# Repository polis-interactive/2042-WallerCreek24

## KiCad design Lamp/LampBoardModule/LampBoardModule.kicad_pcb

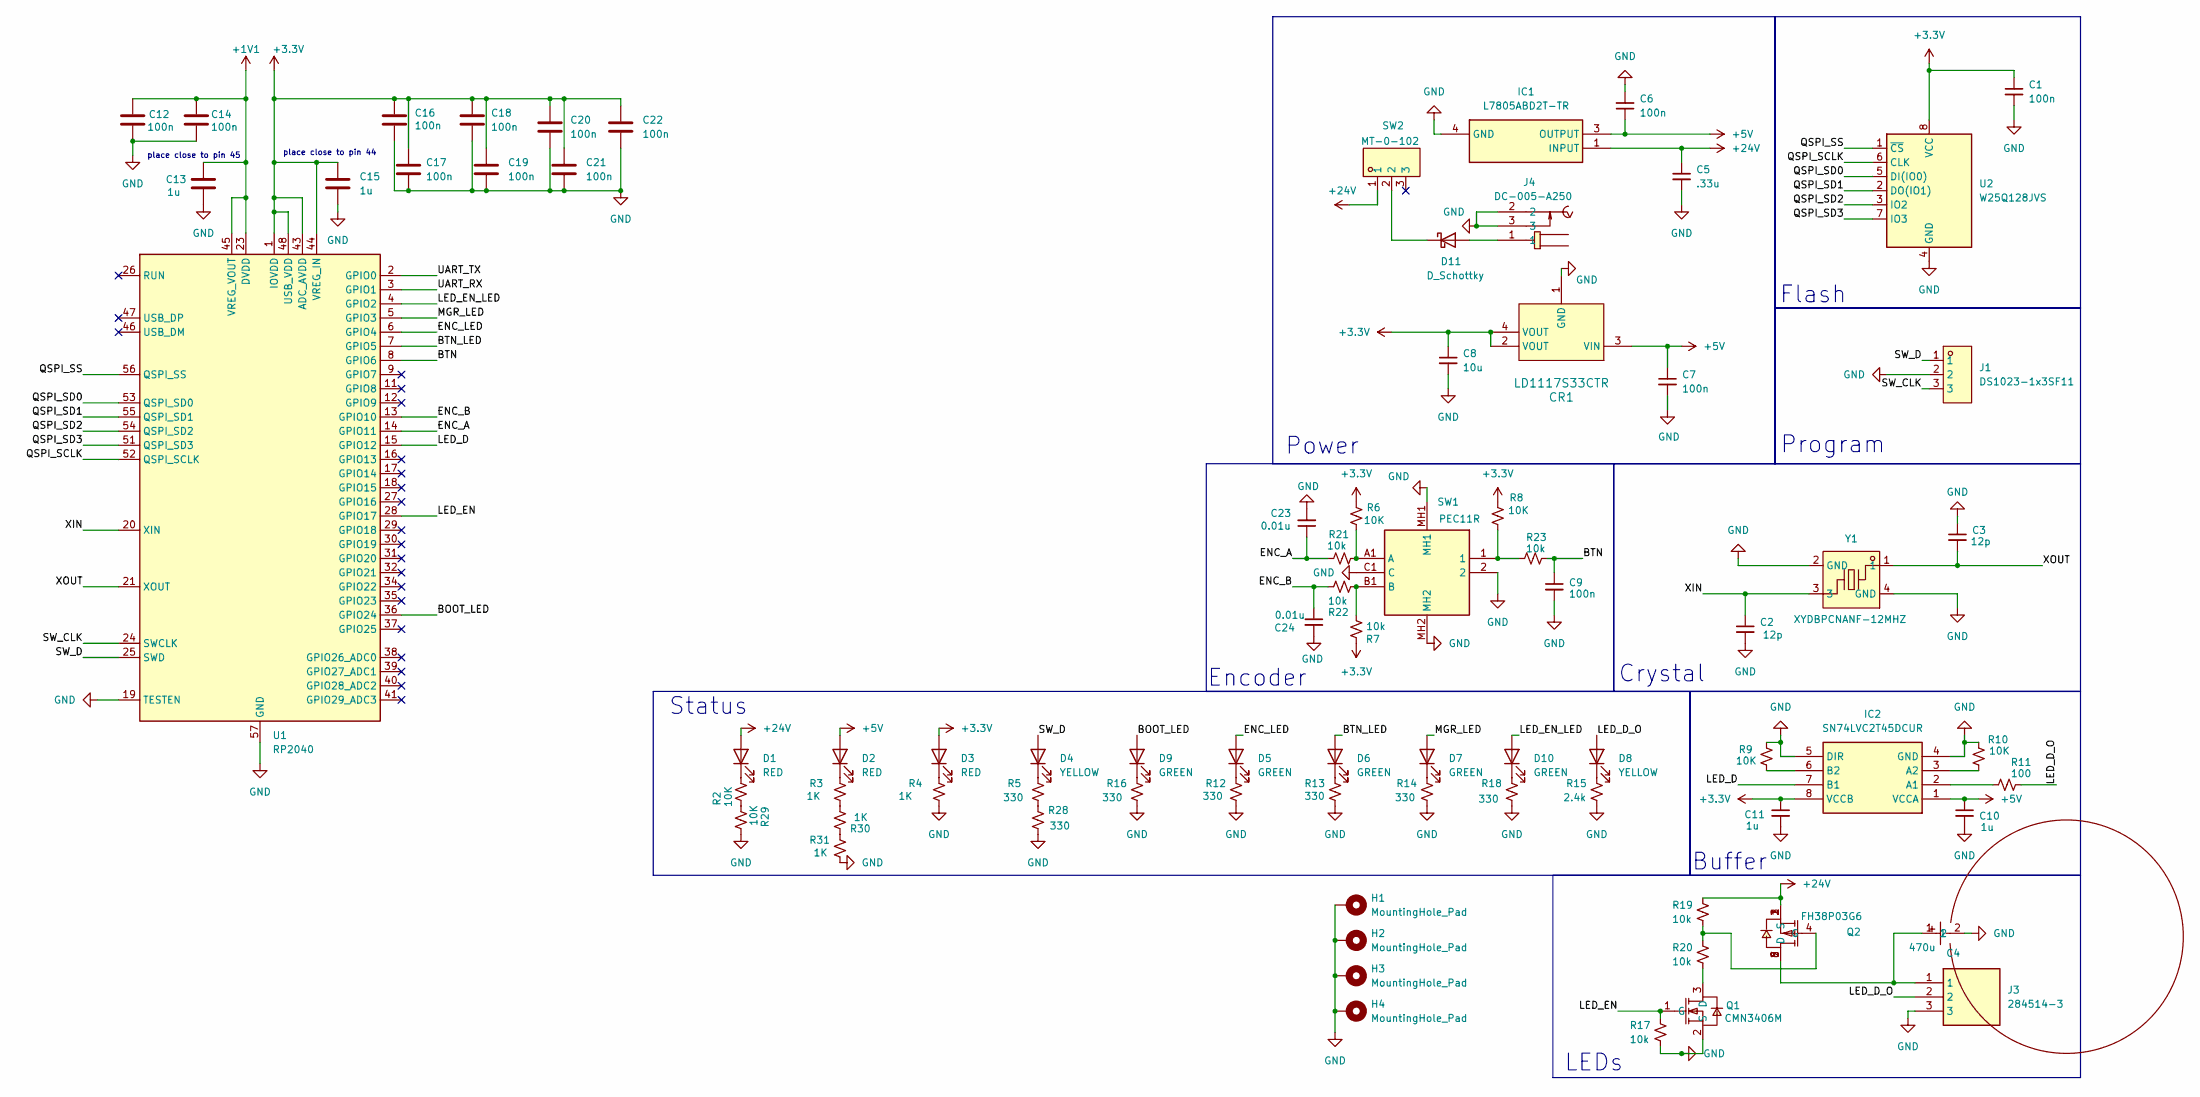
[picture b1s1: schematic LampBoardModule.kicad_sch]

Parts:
C1, C6, C7, C9, C12, C14, C16, C17, C18, C19, C21, C22: 100n; C_0402_1005Metric; LCSC C1525
C2, C3: 12p; C_0402_1005Metric; LCSC C1547
C4: 470u; CAP-TH_BD10.0-P5.00-D1.0-FD; LCSC Part C34642
C5: .33u; C_0805_2012Metric; LCSC C309049
C8: 10u; C_0603_1608Metric; LCSC C92487
C10, C11, C13, C15: 1u; C_0402_1005Metric; LCSC C52923
C20: 100n; C_0402_1005Metric; JLCPCBA Part # C1525
C23, C24: 0.01u; C_0603_1608Metric; LCSC C1589
CR1: LD1117S33CTR; SOT-223-4_L6.5-W3.5-P2.30-LS7.0-BR; LCSC C35879
D1, D2, D3: RED; LED_0603_1608Metric; LCSC C2286
D4, D8: YELLOW; LED_0603_1608Metric; LCSC C965808
D5, D6, D7, D9, D10: GREEN; LED_0603_1608Metric; LCSC C965804
D11: D_Schottky; D_SMA; LCSC C8678
H1, H2, H3, H4: MountingHole_Pad; MountingHole_2.7mm_M2.5_DIN965_Pad
IC1: L7805ABD2T-TR; D2PAK-STB35NF10T4; Mouser Part Number 511-L7805ABD2T-TR
IC2: SN74LVC2T45DCUR; SOP50P310X90-8N; Mouser Part Number 595-SN74LVC2T45DCUR
J1: DS1023-1x3SF11; HDR-TH_3P-P2.54-V-F-1; LCSC Part C7509516
J3: 284514-3; SHDR3W80P0X350_1X3_1250X725X940P; Mouser Part Number 571-284514-3
J4: DC-005-A250; DC-IN-TH_DC-005-A250; LCSC Part C720558
Q1: CMN3406M; SOT-23-3_L2.9-W1.3-P0.95-LS2.4-BR; LCSC Part C5203800
Q2: FH38P03G6; DFN-8_L3.3-W3.3-P0.65-BL-EP; LCSC Part C2929033
R2, R6, R8, R9, R10, R29: 10K; R_0603_1608Metric; LCSC C15401
R3, R4, R30, R31: 1K; R_0402_1005Metric; LCSC C25543
R5, R12, R13, R14, R16, R18, R28: 330; R_0603_1608Metric; LCSC C23138
R7, R17, R19, R20, R21, R22, R23: 10k; R_0603_1608Metric; LCSC C15401
R11: 100; R_0603_1608Metric; LCSC C22775
R15: 2.4k; R_0805_2012Metric; LCSC C17526
SW1: PEC11R; PEC11R4220FS0024; Mouser Part Number 652-PEC11R-4220F-S24
SW2: MT-0-102; SW-TH_MT-0-102-E001-T000-RS-PJ; LCSC Part C1788499
U1: RP2040; QFN-56-1EP_7x7mm_P0.4mm_EP3.2x3.2mm; LCSC C2040
U2: W25Q128JVS; SOIC-8_5.23x5.23mm_P1.27mm; LCSC C97521
Y1: XYDBPCNANF-12MHZ; OSC-SMD_4P-L2.5-W2.0-BL; Mouser Part Number 815-ABM8-272-T3

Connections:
+1V1: C12.1, C13.1, C14.1, U1.23 (DVDD), U1.45 (VREG_VOUT), U1.50 (DVDD)
+3.3V: C1.1, C8.1, C11.1, C15.1, C16.1, C17.1, C18.1, C19.1, C20.1, C21.1, C22.1, CR1.2 (VOUT), CR1.4 (VOUT), D3.2 (A), IC2.8 (VCCB), R6.2, R7.2, R8.2, U1.1 (IOVDD), U1.10 (IOVDD), U1.22 (IOVDD), U1.33 (IOVDD), U1.42 (IOVDD), U1.43 (ADC_AVDD), U1.44 (VREG_IN), U1.48 (USB_VDD), U1.49 (IOVDD), U2.8 (VCC)
+5V: C6.1, C7.1, C10.1, CR1.3 (VIN), D2.2 (A), IC1.3 (OUTPUT), IC2.1 (VCCA)
+24V: C5.1, D1.2 (A), IC1.1 (INPUT), Q2.1 (S), Q2.2 (S), Q2.3 (S), R19.2, SW2.1
/BOOT_LED: D9.2 (A), U1.36 (GPIO24)
/BTN: C9.1, R23.1, U1.8 (GPIO6)
/BTN_LED: D6.2 (A), U1.7 (GPIO5)
/ENC_A: C23.1, R21.1, U1.14 (GPIO11)
/ENC_B: C24.1, R22.2, U1.13 (GPIO10)
/ENC_LED: D5.2 (A), U1.6 (GPIO4)
/LED_D: IC2.7 (B1), U1.15 (GPIO12)
/LED_D_O: D8.2 (A), J3.2, R11.1
/LED_EN: Q1.1 (G), R17.2, U1.28 (GPIO17)
/LED_EN_LED: D10.2 (A), U1.4 (GPIO2)
/MGR_LED: D7.2 (A), U1.5 (GPIO3)
/QSPI_SCLK: U1.52 (QSPI_SCLK), U2.6 (CLK)
/QSPI_SD0: U1.53 (QSPI_SD0), U2.5 (DI(IO0))
/QSPI_SD1: U1.55 (QSPI_SD1), U2.2 (DO(IO1))
/QSPI_SD2: U1.54 (QSPI_SD2), U2.3 (IO2)
/QSPI_SD3: U1.51 (QSPI_SD3), U2.7 (IO3)
/QSPI_SS: U1.56 (QSPI_SS), U2.1 (~CS)
/SW_CLK: J1.3, U1.24 (SWCLK)
/SW_D: D4.2 (A), J1.1, U1.25 (SWD)
/UART_RX: U1.3 (GPIO1)
/UART_TX: U1.2 (GPIO0)
/XIN: C2.1, U1.20 (XIN), Y1.3
/XOUT: C3.2, U1.21 (XOUT), Y1.1
GND: C1.2, C2.2, C3.1, C4.2, C5.2, C6.2, C7.2, C8.2, C9.2, C10.2, C11.2, C12.2, C13.2, C14.2, C15.2, C16.2, C17.2, C18.2, C19.2, C20.2, C21.2, C22.2, C23.2, C24.2, CR1.1 (GND), H1.1, H2.1, H3.1, H4.1, IC1.4 (GND), IC2.4 (GND), IC2.5 (DIR), J1.2, J3.3, J4.2, J4.3, Q1.2 (S), R4.2, R9.1, R10.1, R12.2, R13.2, R14.2, R15.2, R16.2, R17.1, R18.2, R28.1, R29.2, R31.2, SW1.2, SW1.C1 (C), SW1.MH1, SW1.MH2, U1.19 (TESTEN), U1.57 (GND), U2.4 (GND), Y1.2 (GND), Y1.4 (GND)
unnamed: C4.1, J3.1, Q2.5 (D), Q2.6 (D), Q2.7 (D), Q2.8 (D)
unnamed: D1.1 (K), R2.2
unnamed: D2.1 (K), R3.1
unnamed: D3.1 (K), R4.1
unnamed: D4.1 (K), R5.1
unnamed: D5.1 (K), R12.1
unnamed: D6.1 (K), R13.1
unnamed: D7.1 (K), R14.1
unnamed: D8.1 (K), R15.1
unnamed: D9.1 (K), R16.1
unnamed: D10.1 (K), R18.1
unnamed: D11.2 (A), J4.1
unnamed: D11.1 (K), SW2.2
unnamed: IC2.2 (A1), R11.2
unnamed: IC2.3 (A2), R10.2
unnamed: IC2.6 (B2), R9.2
unnamed: Q1.3 (D), R20.1
unnamed: Q2.4 (G), R19.1, R20.2
unnamed: R2.1, R29.1
unnamed: R3.2, R30.2
unnamed: R8.1, R23.2, SW1.1
unnamed: R5.2, R28.2
unnamed: R30.1, R31.1
unnamed: R6.1, R21.2, SW1.A1 (A)
unnamed: R7.1, R22.1, SW1.B1 (B)

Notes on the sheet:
Crystal
place close to pin 44
Buffer
Power
place close to pin 45
LEDs
Flash
Status
Program
Encoder

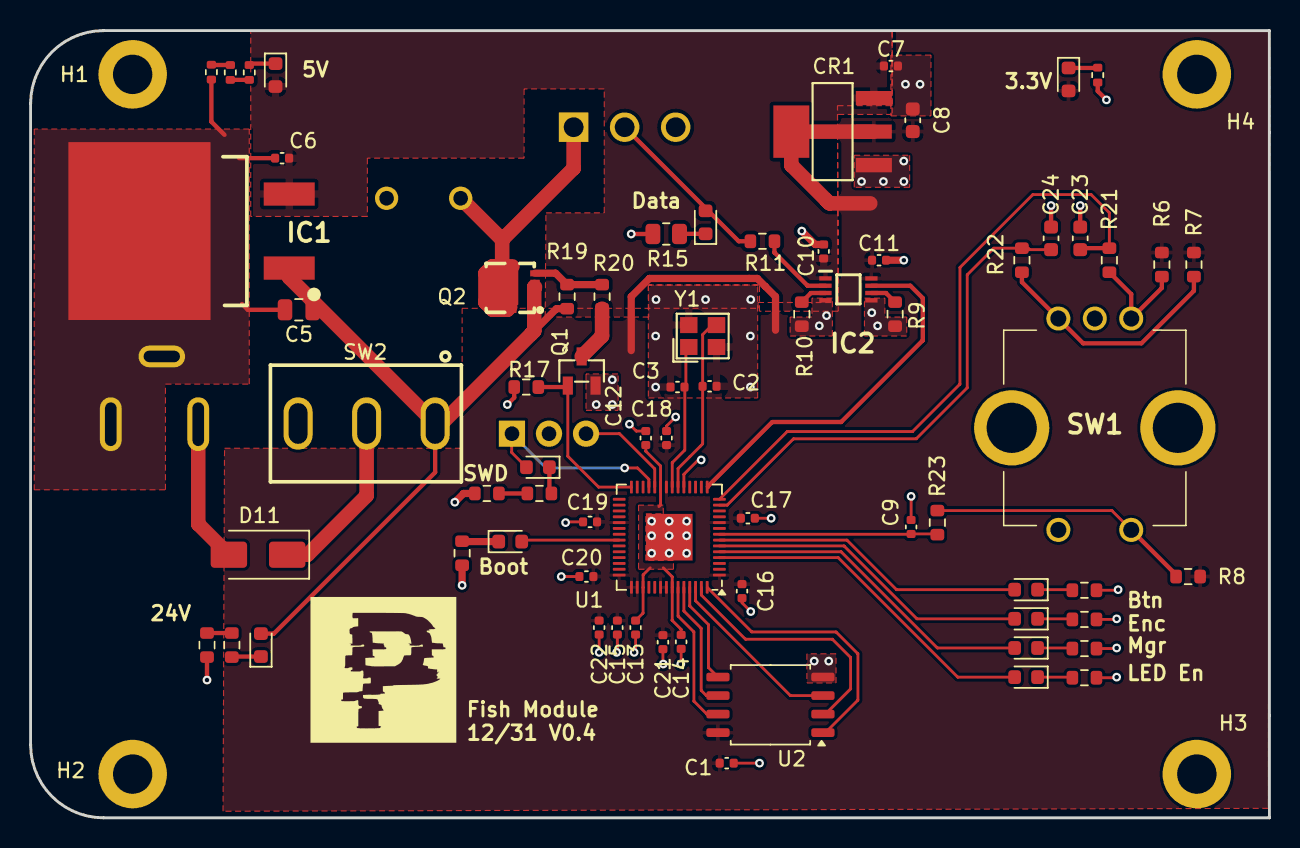
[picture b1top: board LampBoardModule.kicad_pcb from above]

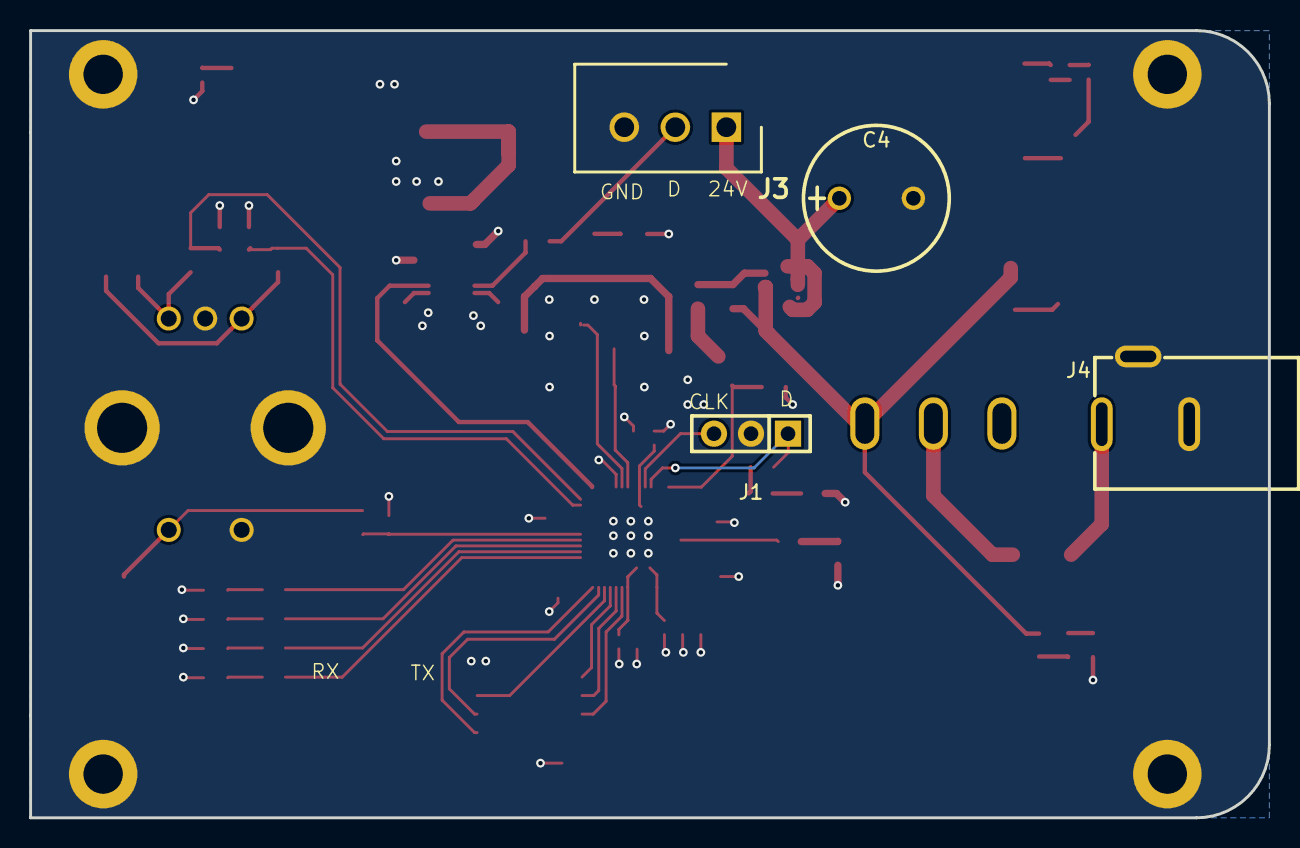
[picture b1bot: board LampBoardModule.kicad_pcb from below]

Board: 2 copper layers, 85.0 x 54.0 mm, 78 parts (4 on the bottom side), 51 nets.

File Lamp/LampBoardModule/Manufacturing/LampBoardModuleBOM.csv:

"Reference","Value","Datasheet","Footprint","Qty","DNP","LCSC","LCSC Part"
"C1,C6,C7,C9,C12,C14,C16,C17,C18,C19,C20,C21,C22","100n","~","Capacitor_SMD:C_0402_1005Metric","13","","C1525","C1525"
"C2,C3","12p","~","Capacitor_SMD:C_0402_1005Metric","2","","C1547","C1547"
"C4","470u","https://lcsc.com/product-detail/Aluminum-Electrolytic-Capaci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","easyeda2kicad:CAP-TH_BD10.0-P5.00-D1.0-FD","1","","C34642","C34642"
"C5",".33u","~","Capacitor_SMD:C_0805_2012Metric","1","","C309049","C309049"
"C8","10u","~","Capacitor_SMD:C_0603_1608Metric","1","","C92487","C92487"
"C10,C11,C13,C15","1u","~","Capacitor_SMD:C_0402_1005Metric","4","","C52923","C52923"
"C23,C24","0.01u","~","Capacitor_SMD:C_0603_1608Metric","2","","C1589","C1589"
"CR1","LD1117S33CTR","https://lcsc.com/product-detail/Low-Dropout-Regulators-LDO_S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","easyeda2kicad:SOT-223-4_L6.5-W3.5-P2.30-LS7.0-BR","1","","C35879","C35879"
"D1,D2,D3","RED","~","LED_SMD:LED_0603_1608Metric","3","","C2286","C2286"
"D4,D8","YELLOW","~","LED_SMD:LED_0603_1608Metric","2","","C965808","C965808"
"D5,D6,D7,D9,D10","GREEN","~","LED_SMD:LED_0603_1608Metric","5","","C965804","C965804"
"D11","D_Schottky","~","Diode_SMD:D_SMA","1","","C8678","C8678"
"IC1","L7805ABD2T-TR","https://www.st.com/resource/en/datasheet/l78.pdf","L7805ABD2T-TR:D2PAK-STB35NF10T4","1","","C86206","C86206"
"IC2","SN74LVC2T45DCUR","http://www.ti.com/lit/gpn/sn74lvc2t45","SN74LVC2T45DCUR:SOP50P310X90-8N","1","","C15741","C15741"
"J1","DS1023-1x3SF11","~","easyeda2kicad:HDR-TH_3P-P2.54-V-F-1","1","","C7509516","C7509516"
"J3","284514-3","https://www.te.com/commerce/DocumentDelivery/DDEController?A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","284514-3:SHDR3W80P0X350_1X3_1250X725X940P","1","","C7466034","C7466034"
"J4","DC-005-A250","~","easyeda2kicad:DC-IN-TH_DC-005-A250","1","","C720558","C720558"
"Q1","CMN3406M","http://www.diodes.com/assets/Datasheets/ds30376.pdf","easyeda2kicad:SOT-23-3_L2.9-W1.3-P0.95-LS2.4-BR","1","","C5203800","C5203800"
"Q2","FH38P03G6","","easyeda2kicad:DFN-8_L3.3-W3.3-P0.65-BL-EP","1","","C2929033","C2929033"
"R2,R6,R8,R9,R10,R29","10K","~","Resistor_SMD:R_0603_1608Metric","6","","C15401","C15401"
"R3,R4,R30,R31","1K","~","Resistor_SMD:R_0402_1005Metric","4","","C25543","C25543"
"R5,R12,R13,R14,R16,R18,R28","330","~","Resistor_SMD:R_0603_1608Metric","7","","C23138","C23138"
"R7,R17,R19,R20,R21,R22,R23","10k","~","Resistor_SMD:R_0603_1608Metric","7","","C15401","C15401"
"R11","100","~","Resistor_SMD:R_0603_1608Metric","1","","C22775","C22775"
"R15","2.4k","~","Resistor_SMD:R_0805_2012Metric","1","","C17526","C17526"
"SW1","PEC11R","https://www.bourns.com/docs/Product-Datasheets/PEC11R.pdf","PEC11R-4220F-S0024:PEC11R4220FS0024","1","","C7435302","C7435302"
"SW2","MT-0-102","~","easyeda2kicad:SW-TH_MT-0-102-E001-T000-RS-PJ","1","","C1788499","C1788499"
"U1","RP2040","https://datasheets.raspberrypi.com/rp2040/rp2040-datasheet.pdf","Package_DFN_QFN:QFN-56-1EP_7x7mm_P0.4mm_EP3.2x3.2mm","1","","C2040","C2040"
"U2","W25Q128JVS","http://www.winbond.com/resource-files/w25q128jv_dtr%20revc%2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","Package_SO:SOIC-8_5.23x5.23mm_P1.27mm","1","","C97521","C97521"
"Y1","XYDBPCNANF-12MHZ","https://lcsc.com/product-detail/SMD-Crystal-Resonators_TAITI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","easyeda2kicad:OSC-SMD_4P-L2.5-W2.0-BL","1","","C521567","C521567"

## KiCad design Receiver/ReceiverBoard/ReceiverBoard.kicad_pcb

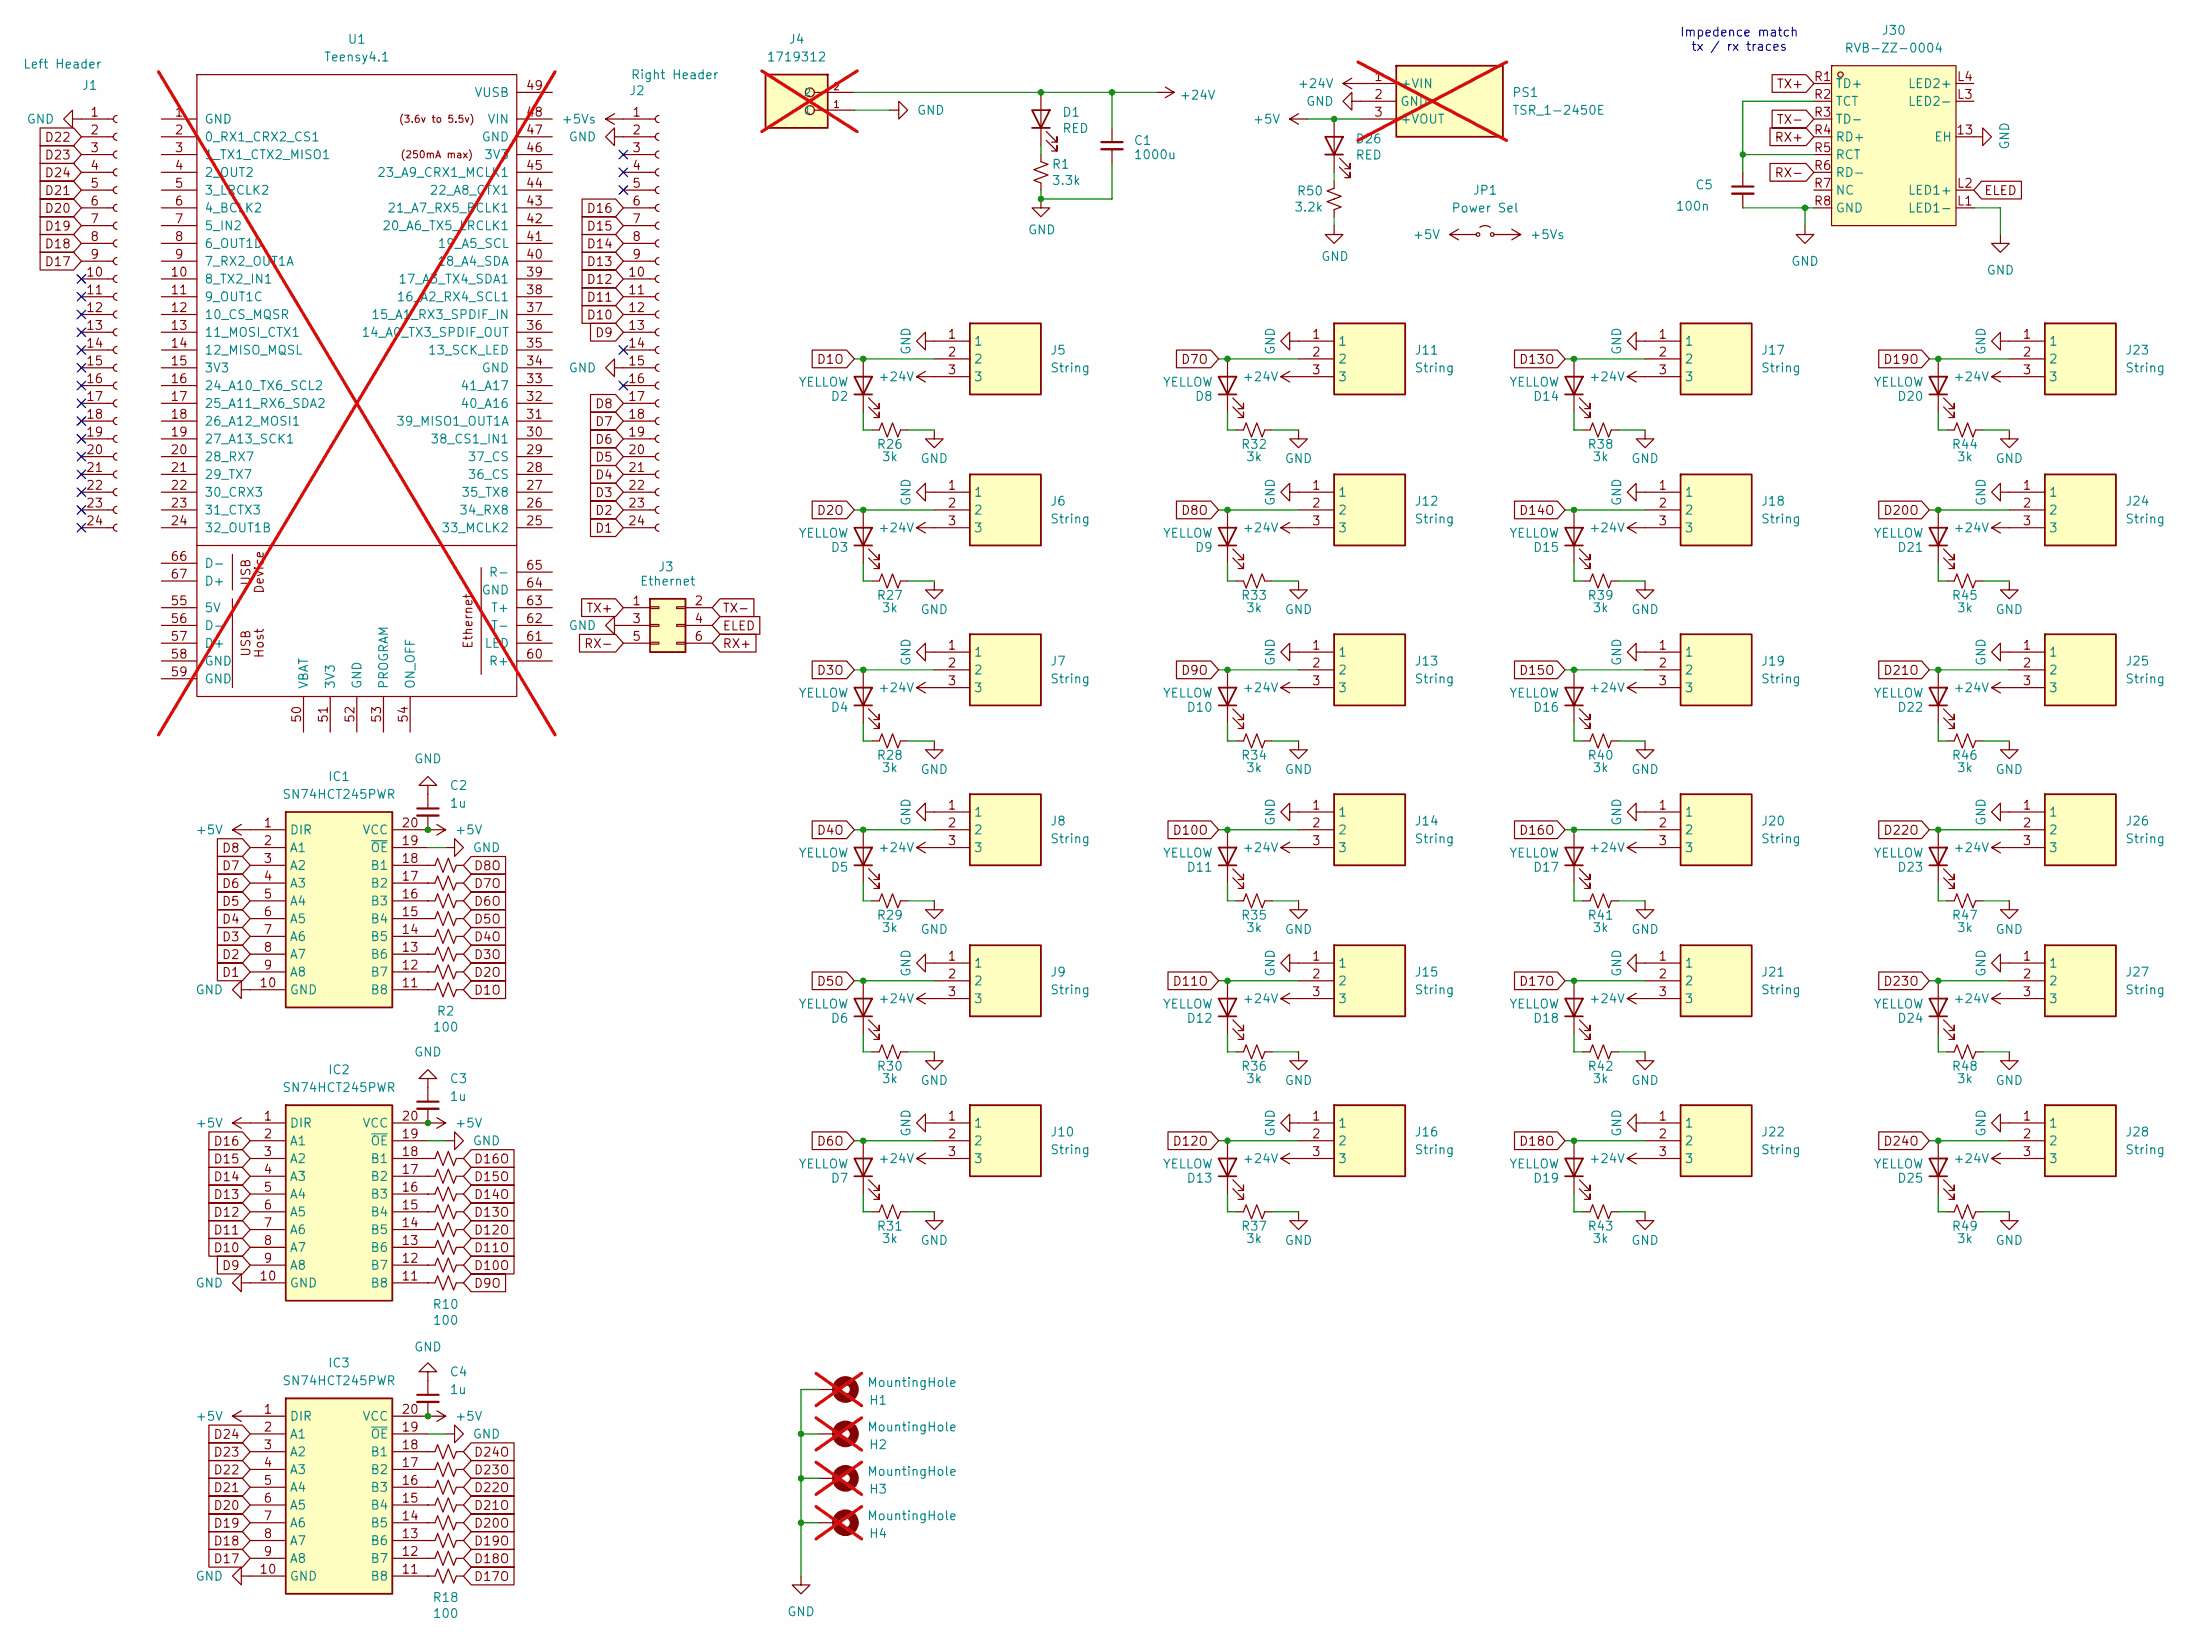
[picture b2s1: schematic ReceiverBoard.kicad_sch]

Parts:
C1: 1000u; C_Radial_D16.0mm_H25.0mm_P7.50mm; LCSC Part # C445417
C2, C3, C4: 1u; C_0603_1608Metric_Pad1.08x0.95mm_HandSolder; LCSC Part # C576859
C5: 100n; C_0603_1608Metric_Pad1.08x0.95mm_HandSolder; LCSC Part # C161854
D1, D26: RED; LED_1206_3216Metric_Pad1.42x1.75mm_HandSolder; LCSC Part # C2984265
D2, D3, D4, D5, D6, D7, D8, D9, D10, D11, D12, D13, D14, D15, D16, D17, D18, D19, D20, D21, D22, D23, D24, D25: YELLOW; LED_0603_1608Metric_Pad1.05x0.95mm_HandSolder; LCSC Part # C72038
H1, H2, H3, H4: MountingHole; MountingHole_3.2mm_M3_Pad; not fitted
IC1, IC2, IC3: SN74HCT245PWR; SOP65P640X120-20N; Mouser Part Number 595-SN74HCT245PWR
J1: Left Header; PinHeader_1x24_P2.54mm_Vertical; LCSC Part # C2883520
J2: Right Header; PinHeader_1x24_P2.54mm_Vertical; LCSC Part # C2883520
J3: Ethernet; PinHeader_2x03_P2.00mm_Vertical; LCSC Part # C2834347
J4: 1719312; PHOENIX_1719312; Mouser Part Number 651-1017521; not fitted
J5, J6, J7, J8, J9, J10, J11, J12, J13, J14, J15, J16, J17, J18, J19, J20, J21, J22, J23, J24, J25, J26, J27, J28: String; SHDR3W80P0X350_1X3_1250X725X940P; Mouser Part Number 571-284514-3
J30: RVB-ZZ-0004; RJ45-TH_RVB-ZZ-0004; Mouser Part Number 950-J1B1211CCD
JP1: Power Sel; PinHeader_1x02_P2.54mm_Vertical; LCSC Part # C3325137
PS1: TSR_1-2450E; TSR12450E; Mouser Part Number 495-TSR1-2450E; not fitted
R1: 3.3k; R_1206_3216Metric_Pad1.30x1.75mm_HandSolder; LCSC Part # C2089480
R2, R3, R4, R5, R6, R7, R8, R9, R10, R11, R12, R13, R14, R15, R16, R17, R18, R19, R20, R21, R22, R23, R24, R25: 100; R_0402_1005Metric_Pad0.72x0.64mm_HandSolder; LCSC Part # C144045
R26, R27, R28, R29, R30, R31, R32, R33, R34, R35, R36, R37, R38, R39, R40, R41, R42, R43, R44, R45, R46, R47, R48, R49: 3k; R_0603_1608Metric_Pad0.98x0.95mm_HandSolder; LCSC Part # C844780
R50: 3.2k; R_1206_3216Metric_Pad1.30x1.75mm_HandSolder; LCSC Part # C2089480
U1: Teensy4.1; Teensy41; not fitted

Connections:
+5V: C2.2, C3.2, C4.2, D26.2 (A), IC1.1 (DIR), IC1.20 (VCC), IC2.1 (DIR), IC2.20 (VCC), IC3.1 (DIR), IC3.20 (VCC), JP1.1 (A), PS1.3 (+VOUT)
+5Vs: J2.1, JP1.2 (B)
+24V: C1.1, D1.2 (A), J4.2, J5.3, J6.3, J7.3, J8.3, J9.3, J10.3, J11.3, J12.3, J13.3, J14.3, J15.3, J16.3, J17.3, J18.3, J19.3, J20.3, J21.3, J22.3, J23.3, J24.3, J25.3, J26.3, J27.3, J28.3, PS1.1 (+VIN)
D1: IC1.9 (A8), J2.24
D1O: D2.2 (A), J5.2, R2.1
D2: IC1.8 (A7), J2.23
D2O: D3.2 (A), J6.2, R3.2
D3: IC1.7 (A6), J2.22
D3O: D4.2 (A), J7.2, R4.2
D4: IC1.6 (A5), J2.21
D4O: D5.2 (A), J8.2, R5.2
D5: IC1.5 (A4), J2.20
D5O: D6.2 (A), J9.2, R6.2
D6: IC1.4 (A3), J2.19
D6O: D7.2 (A), J10.2, R7.2
D7: IC1.3 (A2), J2.18
D7O: D8.2 (A), J11.2, R8.2
D8: IC1.2 (A1), J2.17
D8O: D9.2 (A), J12.2, R9.2
D9: IC2.9 (A8), J2.13
D9O: D10.2 (A), J13.2, R10.1
D10: IC2.8 (A7), J2.12
D10O: D11.2 (A), J14.2, R11.2
D11: IC2.7 (A6), J2.11
D11O: D12.2 (A), J15.2, R12.2
D12: IC2.6 (A5), J2.10
D12O: D13.2 (A), J16.2, R13.2
D13: IC2.5 (A4), J2.9
D13O: D14.2 (A), J17.2, R14.2
D14: IC2.4 (A3), J2.8
D14O: D15.2 (A), J18.2, R15.2
D15: IC2.3 (A2), J2.7
D15O: D16.2 (A), J19.2, R16.2
D16: IC2.2 (A1), J2.6
D16O: D17.2 (A), J20.2, R17.2
D17: IC3.9 (A8), J1.9
D17O: D18.2 (A), J21.2, R18.1
D18: IC3.8 (A7), J1.8
D18O: D19.2 (A), J22.2, R19.2
D19: IC3.7 (A6), J1.7
D19O: D20.2 (A), J23.2, R20.2
D20: IC3.6 (A5), J1.6
D20O: D21.2 (A), J24.2, R21.2
D21: IC3.5 (A4), J1.5
D21O: D22.2 (A), J25.2, R22.2
D22: IC3.4 (A3), J1.2
D22O: D23.2 (A), J26.2, R23.2
D23: IC3.3 (A2), J1.3
D23O: D24.2 (A), J27.2, R24.2
D24: IC3.2 (A1), J1.4
D24O: D25.2 (A), J28.2, R25.2
ELED: J3.4, J30.L2 (LED1+)
GND: C1.2, C2.1, C3.1, C4.1, C5.2, H1.1, H2.1, H3.1, H4.1, IC1.10 (GND), IC1.19 (~OE), IC2.10 (GND), IC2.19 (~OE), IC3.10 (GND), IC3.19 (~OE), J1.1, J2.2, J2.15, J3.3, J4.1, J5.1, J6.1, J7.1, J8.1, J9.1, J10.1, J11.1, J12.1, J13.1, J14.1, J15.1, J16.1, J17.1, J18.1, J19.1, J20.1, J21.1, J22.1, J23.1, J24.1, J25.1, J26.1, J27.1, J28.1, J30.13 (EH), J30.L1 (LED1-), J30.R8 (GND), PS1.2 (GND), R1.2, R26.2, R27.2, R28.2, R29.2, R30.2, R31.2, R32.2, R33.1, R34.2, R35.2, R36.2, R37.2, R38.2, R39.2, R40.2, R41.2, R42.2, R43.2, R44.2, R45.2, R46.2, R47.2, R48.2, R49.2, R50.2
unnamed: D1.1 (K), R1.1
unnamed: D2.1 (K), R26.1
unnamed: D3.1 (K), R27.1
unnamed: D4.1 (K), R28.1
unnamed: D5.1 (K), R29.1
unnamed: D6.1 (K), R30.1
unnamed: D7.1 (K), R31.1
unnamed: D8.1 (K), R32.1
unnamed: D9.1 (K), R33.2
unnamed: D10.1 (K), R34.1
unnamed: D11.1 (K), R35.1
unnamed: D12.1 (K), R36.1
unnamed: D13.1 (K), R37.1
unnamed: D14.1 (K), R38.1
unnamed: D15.1 (K), R39.1
unnamed: D16.1 (K), R40.1
unnamed: D17.1 (K), R41.1
unnamed: D18.1 (K), R42.1
unnamed: D19.1 (K), R43.1
unnamed: D20.1 (K), R44.1
unnamed: D21.1 (K), R45.1
unnamed: D22.1 (K), R46.1
unnamed: D23.1 (K), R47.1
unnamed: D24.1 (K), R48.1
unnamed: D25.1 (K), R49.1
unnamed: D26.1 (K), R50.1
unnamed: IC1.18 (B1), R9.1
unnamed: IC1.17 (B2), R8.1
unnamed: IC1.16 (B3), R7.1
unnamed: IC1.15 (B4), R6.1
unnamed: IC1.14 (B5), R5.1
unnamed: IC1.13 (B6), R4.1
unnamed: IC1.12 (B7), R3.1
unnamed: IC1.11 (B8), R2.2
unnamed: IC2.18 (B1), R17.1
unnamed: IC2.17 (B2), R16.1
unnamed: IC2.16 (B3), R15.1
unnamed: IC2.15 (B4), R14.1
unnamed: IC2.14 (B5), R13.1
unnamed: IC2.13 (B6), R12.1
unnamed: IC2.12 (B7), R11.1
unnamed: IC2.11 (B8), R10.2
unnamed: IC3.18 (B1), R25.1
unnamed: IC3.17 (B2), R24.1
unnamed: IC3.16 (B3), R23.1
unnamed: IC3.15 (B4), R22.1
unnamed: IC3.14 (B5), R21.1
unnamed: IC3.13 (B6), R20.1
unnamed: IC3.12 (B7), R19.1
unnamed: IC3.11 (B8), R18.2
unnamed: C5.1, J30.R2 (TCT), J30.R5 (RCT)
RX+: J3.6, J30.R4 (RD+)
RX-: J3.5, J30.R6 (RD-)
TX+: J3.1, J30.R1 (TD+)
TX-: J3.2, J30.R3 (TD-)

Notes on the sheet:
Impedence match tx / rx traces

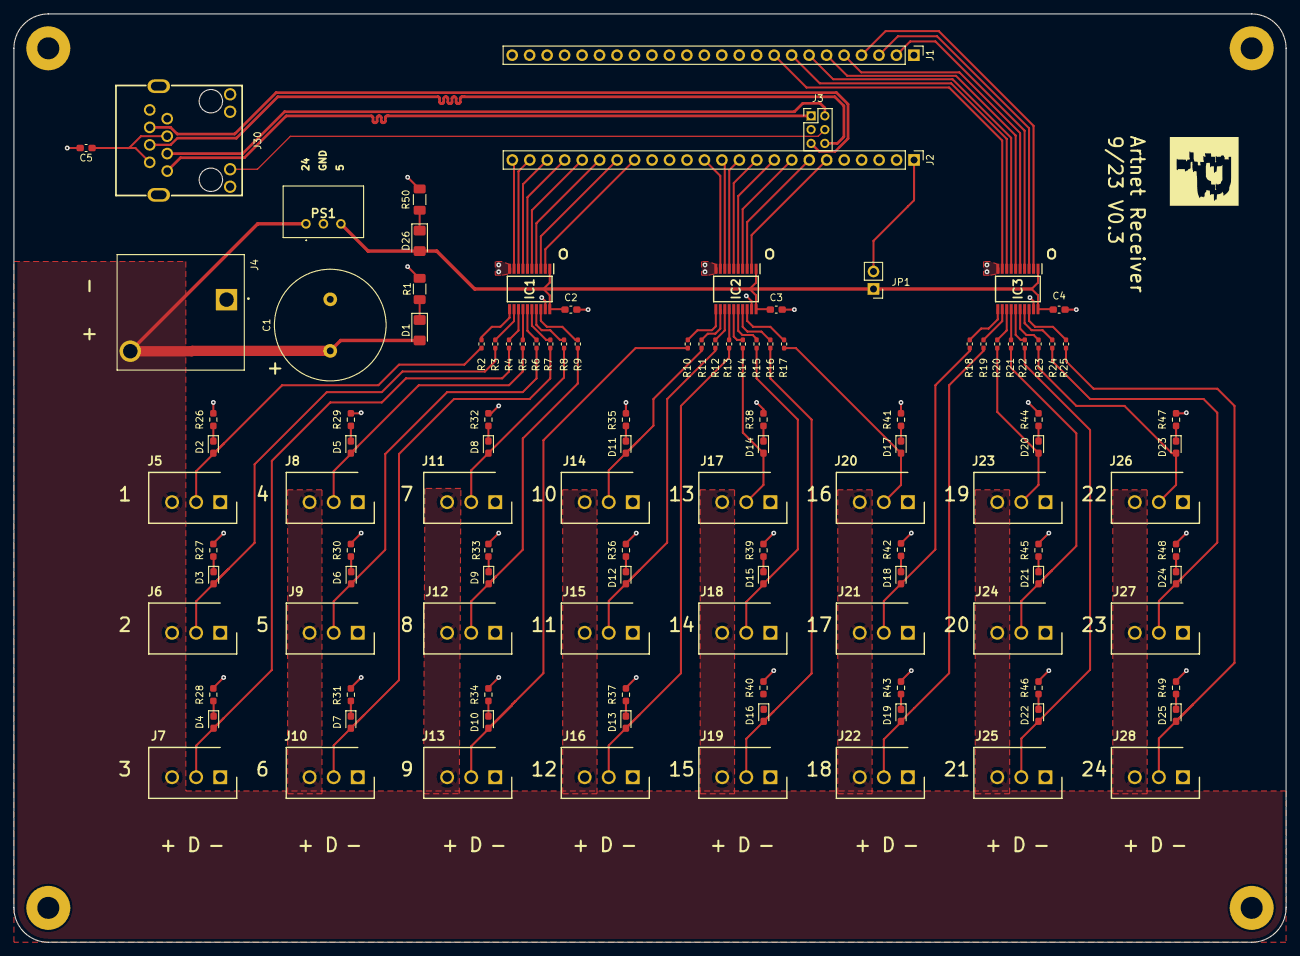
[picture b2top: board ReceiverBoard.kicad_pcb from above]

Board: 2 copper layers, 185.0 x 135.0 mm, 119 parts (0 on the bottom side), 108 nets.

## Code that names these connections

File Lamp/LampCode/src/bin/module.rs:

#![no_std]
#![no_main]

use embassy_rp::flash::{Async, Flash, ERASE_SIZE};
use lamp::{load_store, Debouncer, button_task, encoder_task, lights_task, manager_task};

use defmt::*;

use embassy_executor::Spawner;
use embassy_time::{Duration, Timer};
use embassy_rp::bind_interrupts;
use embassy_rp::gpio::{Input, Level, Output, Pull};
use embassy_rp::peripherals::{self, PIO0};
use embassy_rp::pio::{InterruptHandler, Pio};
use embassy_rp::pio_programs::ws2812::{PioWs2812, PioWs2812Program};
use embassy_rp::pio_programs::rotary_encoder::{PioEncoder, PioEncoderProgram};
use embassy_rp::watchdog::Watchdog;

use {defmt_rtt as _, panic_probe as _};


use assign_resources::assign_resources;

assign_resources! {
  boot: BootResources {
    led_pin: PIN_24
  }
  encoder: EncoderResources {
    a_pin: PIN_10,
    b_pin: PIN_11,
    led_pin: PIN_4  
  }
  button: ButtonResources {
    pin: PIN_6,
    led_pin: PIN_5
  }
  manager: ManagerResources {
    led_pin: PIN_3
  }
  led: LedResources {
    data_pin: PIN_12,
    dma_chan: DMA_CH1,
    en_pin: PIN_17,
    en_led_pin: PIN_2
  },
  flash: FlashResources {
    dma_chan: DMA_CH0
  }
}

bind_interrupts!(struct Irqs {
  PIO0_IRQ_0 => InterruptHandler<PIO0>;
});

const ADDR_OFFSET: u32 = 0x100000;
const FLASH_SIZE: u32 = 2 * 1024 * 1024;
const _FLASH_SIZE: usize = FLASH_SIZE as usize;

#[embassy_executor::main]
async fn main(spawner: Spawner) {

  info!("Running main");

  
  info!("Initializing embassy");

  let p = embassy_rp::init(Default::default());
  let r = split_resources! {p};

  info!("Showing signs of life");

  let mut boot_led = Output::new(r.boot.led_pin, Level::High);
  
  info!("Start Watchdog");

  let mut watchdog = Watchdog::new(p.WATCHDOG);
  watchdog.start(Duration::from_millis(2_000));


  info!("Initialize State");

  let mut flash = Flash::<_, Async, _FLASH_SIZE>::new(p.FLASH, r.flash.dma_chan);
  let flash_range_start = (flash.capacity() - 4 as usize * ERASE_SIZE) as u32;
  let flash_range_end = flash.capacity() as u32;
  let map_flash_range = flash_range_start..flash_range_end;
  load_store(&mut flash, map_flash_range.clone()).await;

  info!("Initialize, start up button");

  let btn = Debouncer::new(Input::new(r.button.pin, Pull::Up), Duration::from_millis(20));  
  let btn_led = Output::new(r.button.led_pin, Level::Low);
  spawner.must_spawn(button_task(btn, btn_led));

  // encoder / leds
  
  let Pio {
    mut common, sm0, sm1, ..
  } = Pio::new(p.PIO0, Irqs);

  info!("Initialize, start up encoder");

  let enc_prg = PioEncoderProgram::new(&mut common);
  let enc = PioEncoder::new(&mut common, sm0, r.encoder.a_pin, r.encoder.b_pin, &enc_prg);
  let enc_led = Output::new(r.encoder.led_pin, Level::Low);
  spawner.must_spawn(encoder_task(enc, enc_led, false));

  info!("Initialize, start up leds");

  let lts_prg = PioWs2812Program::new(&mut common);
  let lts = PioWs2812::new(&mut common, sm1, r.led.dma_chan, r.led.data_pin, &lts_prg);
  let en = Output::new(r.led.en_pin, Level::Low);
  let en_led = Output::new(r.led.en_led_pin, Level::Low);
  spawner.must_spawn(lights_task(lts, en, en_led));

  info!("Initialize, start manager");

  let mng_led = Output::new(r.manager.led_pin, Level::Low);
  spawner.must_spawn(manager_task(spawner, mng_led, flash, map_flash_range));

  info!("Main task finished; feeding watchdog");

  loop {
    Timer::after_secs(1).await;
    watchdog.feed();
    boot_led.toggle();
  }
}

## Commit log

2024-10-14 Artnet is up and running!
2024-10-17 Started interaction code; fixed receiver code
2024-10-18 Fixed controller output; don't know if I'll limit to strings or just make them output the full 24 but meh
2024-10-28 dunno, paranoid
2024-10-31 Uploading to download on mac
2024-10-31 Fixed dirty universe
2024-11-01 Updated receiver to never DHCP me
2024-11-02 Added gamma correction, white correction
2024-11-02 Updated fustion export spline
2024-11-02 Added T spline
2024-11-08 Waves didn't work; leaving this here so we have it before I get rid of them
2024-11-08 two functional states...
2024-11-08 No r for now, stopping point
2024-11-08 Added switch
2024-11-08 Welp, that didn't work
2024-11-11 dunno, send it
2024-11-12 Pretty decent fades; might need to dial it in
2024-11-21 Worked well for install, will need tweaks to work with final
2024-11-24 Saving my spot incase rework is impossible
2024-11-26 boards are done
2024-12-23 Final version ready to roll
2025-01-06 Finished lamp saving; cad v0.4
2025-01-11 Getting warmer, but I think I have a bug somewhere...
2025-01-16 Small tweaks after losing my mind
2025-01-17 Got the value switching going; next to actually randomly walk
2025-01-20 Walker away!
2025-01-20 Updated readme instructions
2025-01-20 not going to use this, but probs inspo; need to make hold configs discreet
2025-01-20 Made value min / max light brightness
2025-01-25 Okay, I broke walker, but rainbow is almost there; need to change the step to 255 so spread can vary linearly
2025-01-26 Rainbow is working great; moving to fixing walker
2025-01-26 Walker is working again, but I think something isn't right...
2025-01-26 I GOT IT WORKING
2025-06-10 rgb white looks bad...
